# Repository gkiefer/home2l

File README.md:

What are the *Home2Ls*?
=======================

The *Home2L `[houmtu:l]`* suite is a collection of tools and libraries for automation in private homes. Its main features are:

* **_Home2L Resources_**: Novel concept to integrate and manage sensors, actors or services of any kind **efficiently and precisely**.

* **Automation rules written in Python** - but not limited to that.

* **Easy integration of services and new devices** - via MQTT, in C/C++, Python or by a shell script.

* **_Home2L Brownies_**: Simple and efficient **automation bus to interconnect cheap 8-bit microcontrollers**
  for do-it-yourself sensor or actor hardware.

* **_Home2L WallClock_**: **Lightweight, concise, and responsive information display**,
  suitable to be installed on cheap tablets or minicomputers and mounted in all rooms - just like a wall clock.

* **Interactive floor plan** for all kinds of gadgets (windows, shades, lights, phones, computers, services, ...).

* **Video door phone** and **inter-room communication** (SIP-based).

* **Playing music** anywhere at home (MPD-based).

* **Family calendar** (in *WallClock*).

* **Docker image** and improved tutorial for getting started quickly.

What is New?
============

* WallClock: Power meter for votovoltaic systems

* WallClock: User-configurable floorplan icons

* WallClock: Improved and more self-contained Android app

* MQTT bridge: Support for JSON payloads

* New drivers: Fingerprint, Fronius

* Many small improvements and some bug fixes

How Can I Try It? Get More Information?
=======================================

The main place of documentation is the [*Home2L Book*](home2l-book.pdf).
The APIs for developing rules and drivers or to extend the *Home2Ls* are documented with Doxygen:
[C/C++ API](home2l-api_c/index.html), [Python API](home2l-api_python/index.html).

The suite comes with a [Docker Demo Image](https://hub.docker.com/r/gkiefer/home2l) allowing to test the suite easily.
The [*Home2L Book*](home2l-book.pdf) contains a **a step-by-step tutorial demonstrating the key features of the *Home2L* suite**.

**For the brave and the impatient:**

    $ xhost +local:  # allow X11 applications to open windows
    $ docker run -ti --rm \
      --name home2l-showcase --hostname home2l-showcase \
      -e DISPLAY=$DISPLAY -v /tmp/.X11-unix:/tmp/.X11-unix \
      --ipc=host --device /dev/snd \
      gkiefer/home2l

What is Special About the *Home2Ls*?
====================================

## Versatile *Resources* Library

The central component of the *Home2L* suite is the *Resources* library. It connects physical sensors and actors, software services, computers and more. Everything that can act or sense in the widest sense, can be modelled as a *resource* in the *Home2L* suite.

All *resources* are arranged in a common namespace, but driven and accessed in a completely distribited way from any computer. They can be manipulated or read out using the library, which provides full network transparency and supports arbitrary concurrent accesses from any process on any machine anytime.

Resources are manipulated by means of independent *requests* with individual attributes like priorities and time intervals. The user pushes a button to open the window blinds. One second later, a timer-triggered automatic rule tells the blinds to close. What should happen now? The *request* model allows to clearly specify priorities (e.g. user interaction in favor of automation rules) and to handle concurrency properly.

The *Home2L Shell* is a powerful administration tool and allows to access resources and submit requests on the command line or by shell scripts.

Both automation rules and resource drivers can also be part of a larger program. Any software linking against the *Resources* library can access resources or publish own run-time information as resources.

## Efficient and Lightweight Design

All core components are written in C/C++, with a very minimum set of external dependencies beyond *libc* - ideally suited for small embedded devices and microcontrollers. There is no need for a Java runtime environment or a heavy web framework. Starting up a server and a command shell and shutting both down again takes less than a second altogether - on an ARM-based minicomputer running at 144 MHz!

The *Home2L WallClock* is written in native code (C++) and only uses *SDL2* for its UI toolkit. This makes it very portable and lightweight. Low-cost, low-performance minicomputers or Android tablets can be used as end-user devices, there is no need to install and regularly update a full-featured web browser on them.

## Ambient Intelligence, No Need for a Central Server

Central servers are single points of failure. *Home2L* follows a completely distributed concept. Any (mini-)computer can act as part of the network. If resources, such as sensors or actors, are connected to them, they can be exported to any other host in the *Home2L* network. A failure of a host only causes its own resources to be unavailable - everything else keeps on working.

## Automation Rules Written in Python - But Not Limited to That

There is no new language or tool to learn to formulate automation rules. *Home2L* rules written in Python profit from the simplicity and power of the Python language. There can be multiple rules scripts, they can run on any machine, and they may be combined with other software routines or be part of larger applications.

Other ways to interact with *Home2L* resources is via the C/C++ API from any application or by shell scripts using the *Home2L Shell*.

## Integrating Sensors/Actor Hardware and Services: MQTT, Python, Shell Scripts, ...

MQTT-enabled devices can be imported directly using the MQTT gateway driver.

An API for *resource* drivers allows to easily add support for new hardware or services. A driver can be implemented

- in native C/C++ code,
- as a shell script,
- in Python.

For all three cases, documented examples are available in the source tree.

## Easy Integration of Do-It-Yourself Hardware

*Home2L Brownies* are programmed low-cost microcontrollers (*AVR ATtiny 84/85/861*) connected to a Linux host over 4-wire cables (e.g. KNX/EIB cables). The bus protocol is based on *i2c*, robust and allows to build very simple, self-made hardware nodes. Just an *ATtiny* device and two resistors are enough to build a sensor node! Additional circuitry such as crystal clock generators, transceivers or voltage regulators are not necessary.

*Home2L Brownies* can drive, for example, window/door/light sensors (GPIOs), temperature sensors, or window shades/actuators.

The *Home2L* suite includes a software stack for the Linux (host) and for the microcontroller (device) side. The protocol includes various mechanisms for error correction/avoidance, host notification, as well as a variety of maintenance tools for remote configuration, diagnosis, collection of statistics, remote software updates, and device resurrection for the case that a software update failed and the device is difficult to reach physically.

## Privacy

The *Home2Ls* do not need an Internet connection and do not try to communicate with hosts other than they are configured to. By design, the *Home2Ls* communicate with each other over a (trusted) LAN, which can easily be set up and secured using standard Linux/UNIX techniques. The open source licensing ensures transparency for what the software does inside the user's private home.

## Modularity

The core part, the *Resources* library, is kept small and portable with APIs for application programs *and* drivers in C/C++ and Python. All other components are optional and can be used or replaced by alternatives as desired by the user.

How can I Help?
===============

The code has been published with the hope that is useful to the community. To let the project grow further and make available to a broader audience, **volunteers and partners are welcome**.

Great contributions are:

- **Report and help fixing bugs.**

- Make **sample installations**, document them and share your experiences.

- **Packaging**: Create packages for major Linux distributions.

- **Documentation**: Write good documentation, particularly for end users.

For any questions on how to participate, do not hesitate to contact us directly.

Questions?
==========

Feel free to contact: Gundolf Kiefer `<gundolf.kiefer@web.de>`

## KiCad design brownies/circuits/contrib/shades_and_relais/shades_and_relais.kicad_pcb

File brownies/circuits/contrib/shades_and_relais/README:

Circuit:  shades_and_relais/README
Author:   Axel Rau <Axel.Rau+home2l@Chaos1.DE>
Date:     2022-07-29
Updated:  2024-05-27

Description:
  Window Control Board suited for housing CAMDENBOSS CBEAC-03-WH.
  https://www.reichelt.de/elektronikgehaeuse-130x80x45-mm-weiss-cb-eac-03-wh-p317686.html
  It drives one shade with its relais (J1) and has sensors for "window closed"
  (J1 9), "window locked" (J1 8), sun sensor (J1 11) and "shade down and
  "shade up" (J1 6,7), with both wires optional terminated by opto couplers,
  to allow long wirings.
  
  A suitable firmware definition in Family.mk is winl:
  
  # winl: Window brownie; supports temperature sensor and single shade with lock,
  # close and sun sensors (PA3, PA7 and PB2)
  #   - circuit: 'minishades' and 'shades_and_relais'
  ifeq ($(BROWNIE_VARIANT),winl)
  	BROWNIE_CFG ?= WITH_TEMP_ZACWIRE=1 SHADES_PORTS=1 GPIO_IN_PRESENCE=0xc8 GPIO_IN_PULLUP=0xc8 
  	# SHADES_TIMEOUT=0 TWI_SL_NOTIFY=0
  endif

KiCad version: 8

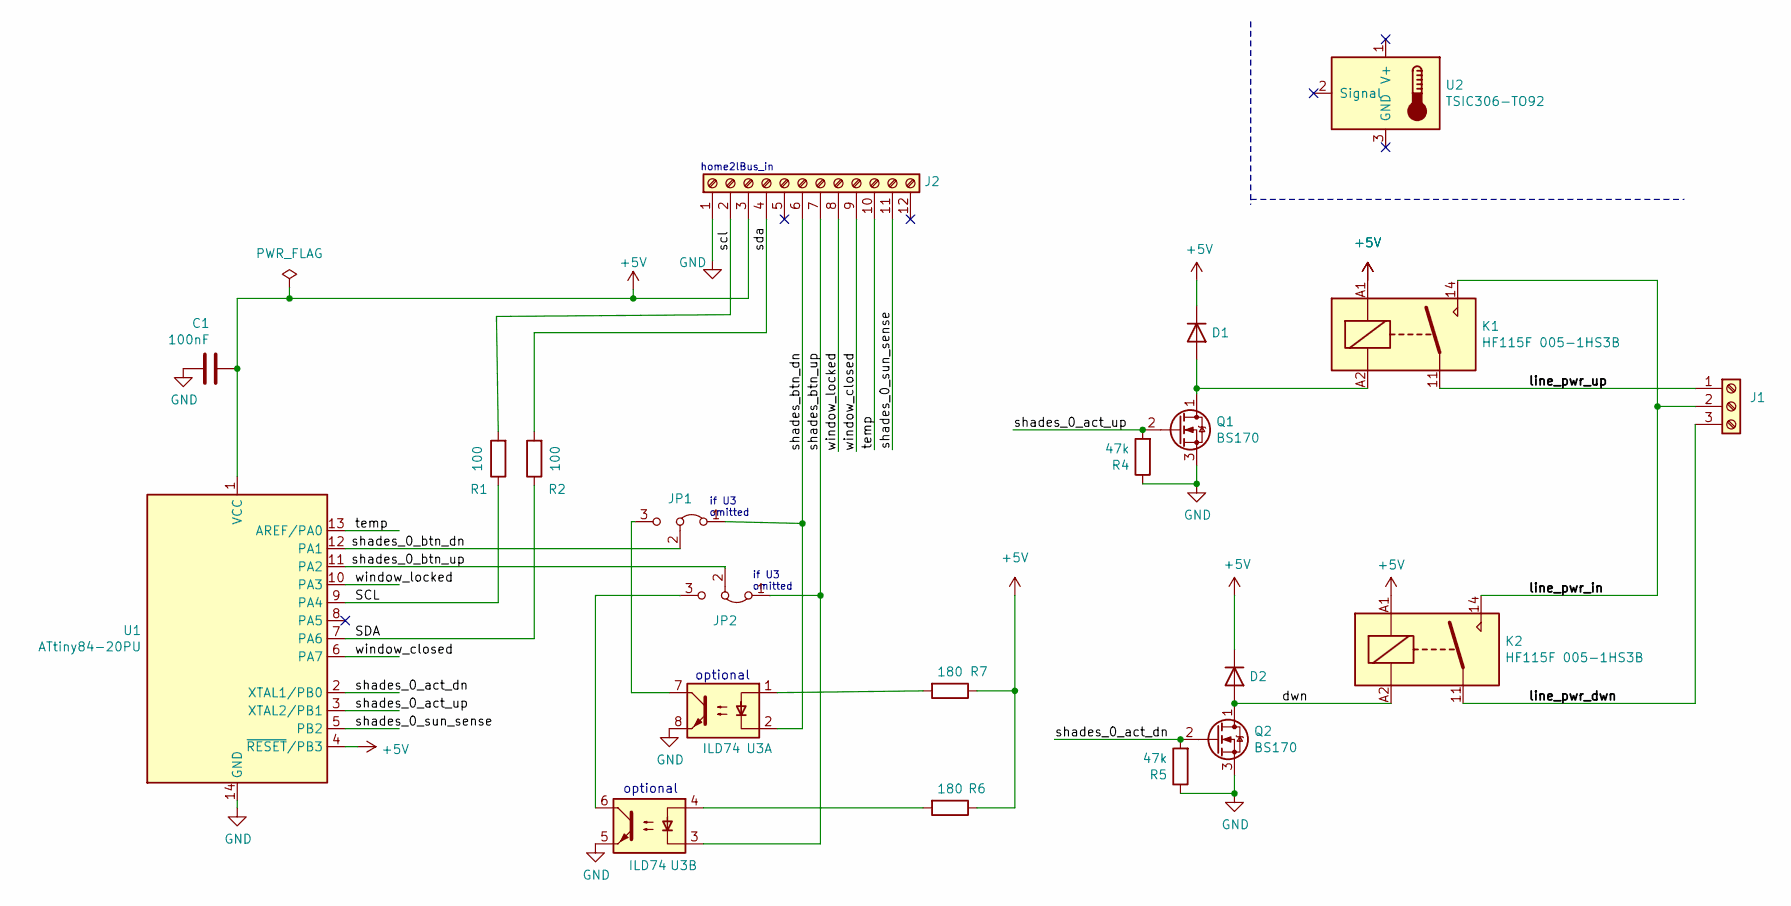
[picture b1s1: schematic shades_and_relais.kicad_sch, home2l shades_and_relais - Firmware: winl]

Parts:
C1: 100nF; C_Disc_D4.3mm_W1.9mm_P5.00mm
D1, D2: 1N400X; D_T-1_P5.08mm_Horizontal
J1: TerminalBlock_bornier-3_P5.08mm
J2: TerminalBlock_Phoenix_MPT-0,5-12-2.54_1x12_P2.54mm_Horizont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
JP1, JP2: PinHeader_1x03_P2.54mm_Vertical
K1, K2: HF115F 005-1HS3B; Relay_SPST_Schrack-RP-II-1-16A-FormA_RM5mm
Q1, Q2: BS170; TO-92_Inline_Wide
R1, R2: 100; R_Axial_DIN0204_L3.6mm_D1.6mm_P7.62mm_Horizontal
R4, R5: 47k; R_Axial_DIN0204_L3.6mm_D1.6mm_P7.62mm_Horizontal
R6, R7: 180; R_Axial_DIN0204_L3.6mm_D1.6mm_P7.62mm_Horizontal
U1: ATtiny84-20PU; DIP-14_W7.62mm_Socket
U2: TSIC306-TO92; TO-92_Inline_Wide
U3: ILD74; DIP-8_W7.62mm

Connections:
+5V: C1.1, D1.1 (K), D2.1 (K), J2.3, K1.A1, K2.A1, R6.1, R7.1, U1.1 (VCC), U1.4 (~RESET/PB3)
/SCL: R1.1, U1.9 (PA4)
/SDA: R2.1, U1.7 (PA6)
/dwn: D2.2 (A), K2.A2, Q2.1 (D)
/line_pwr_dwn: J1.3, K2.11
/line_pwr_in: J1.2, K1.14, K2.14
/line_pwr_up: J1.1, K1.11
/scl: J2.2, R1.2
/sda: J2.4, R2.2
/shades_0_act_dn: Q2.2 (G), R5.2, U1.2 (XTAL1/PB0)
/shades_0_act_up: Q1.2 (G), R4.2, U1.3 (XTAL2/PB1)
/shades_0_btn_dn: JP1.2 (C), U1.12 (PA1)
/shades_0_btn_up: JP2.2 (C), U1.11 (PA2)
/shades_0_sun_sense: J2.11, U1.5 (PB2)
/shades_btn_dn: J2.6, JP1.1 (A), U3.2
/shades_btn_up: J2.7, JP2.1 (A), U3.3
/temp: J2.10, U1.13 (AREF/PA0)
/window_closed: J2.9, U1.6 (PA7)
/window_locked: J2.8, U1.10 (PA3)
GND: C1.2, J2.1, Q1.3 (S), Q2.3 (S), R4.1, R5.1, U1.14 (GND), U3.5, U3.8
unnamed: D1.2 (A), K1.A2, Q1.1 (D)
unnamed: JP1.3 (B), U3.7
unnamed: JP2.3 (B), U3.6
unnamed: R6.2, U3.4
unnamed: R7.2, U3.1

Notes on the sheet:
optional
if U3 omitted
home2lBus_in

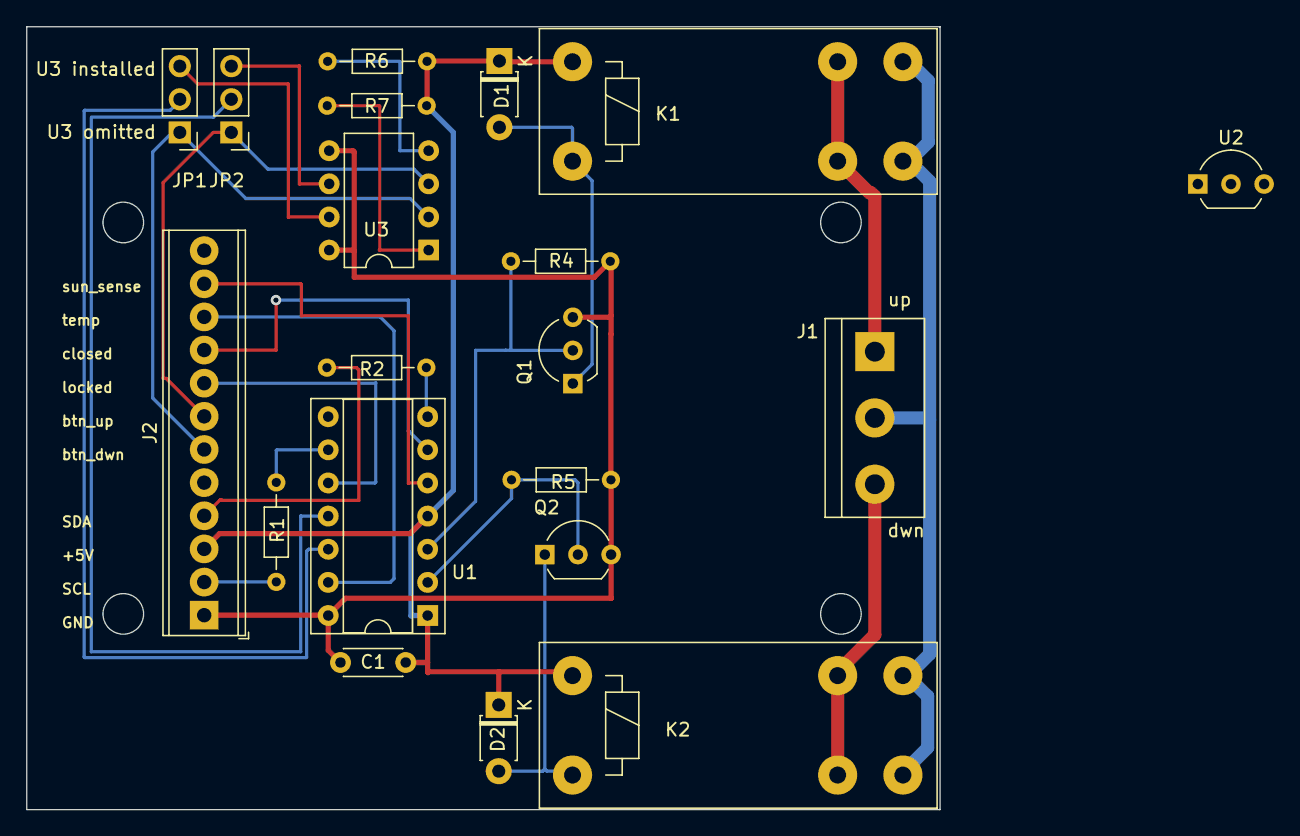
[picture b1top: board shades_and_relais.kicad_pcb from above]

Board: 2 copper layers, 70.0 x 60.0 mm, 20 parts (0 on the bottom side), 25 nets.

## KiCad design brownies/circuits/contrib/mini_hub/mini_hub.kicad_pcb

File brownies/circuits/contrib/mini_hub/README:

Circuit:  mini_hub
Author:   Axel Rau <Axel.Rau+home2l@Chaos1.DE>
Date:     2022-07-29
Updated:  2024-05-26

Description:
  Tiny B-hub Board suited for Spelsberg connection box Q 4-L (33490401).
  
KiCad version: 8

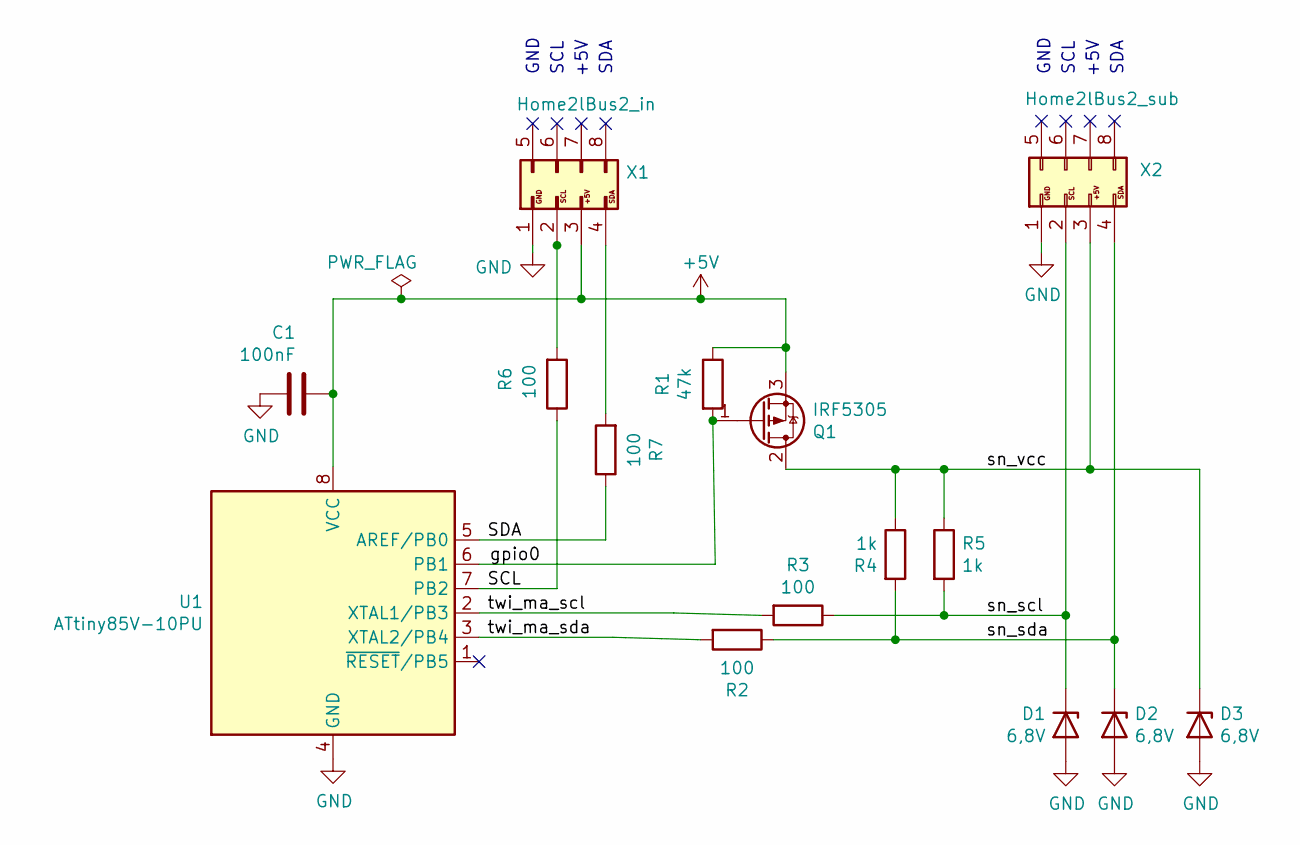
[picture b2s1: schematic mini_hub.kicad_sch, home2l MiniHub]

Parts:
C1: 100nF; C_Disc_D4.3mm_W1.9mm_P5.00mm
D1, D2, D3: 6,8V; D_DO-34_SOD68_P7.62mm_Horizontal
Q1: IRF5305; TO-220-3_Vertical
R1: 47k; R_Axial_DIN0207_L6.3mm_D2.5mm_P7.62mm_Horizontal
R2, R3, R6, R7: 100; R_Axial_DIN0207_L6.3mm_D2.5mm_P7.62mm_Horizontal
R4, R5: 1k; R_Axial_DIN0207_L6.3mm_D2.5mm_P7.62mm_Horizontal
U1: ATtiny85V-10PU; DIP-8_W7.62mm_Socket
X1: Home2lBus2_in; PinHeader_Home2lBus2_in
X2: Home2lBus2_sub; PinSocket_Home2lBus2_sub

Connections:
+5V: C1.1, Q1.3 (S), R1.1, U1.8 (VCC), X1.3
/SCL: R6.1, U1.7 (PB2)
/SDA: R7.1, U1.5 (AREF/PB0)
/gpio0: Q1.1 (G), R1.2, U1.6 (PB1)
/sn_scl: D1.1 (K), R3.1, R5.2, X2.2
/sn_sda: D2.1 (K), R2.1, R4.2, X2.4
/sn_vcc: D3.1 (K), Q1.2 (D), R4.1, R5.1, X2.3
/twi_ma_scl: R3.2, U1.2 (XTAL1/PB3)
/twi_ma_sda: R2.2, U1.3 (XTAL2/PB4)
GND: C1.2, D1.2 (A), D2.2 (A), D3.2 (A), U1.4 (GND), X1.1, X2.1
unnamed: R6.2, X1.2
unnamed: R7.2, X1.4

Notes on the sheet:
SCL
SDA
GND
+5V

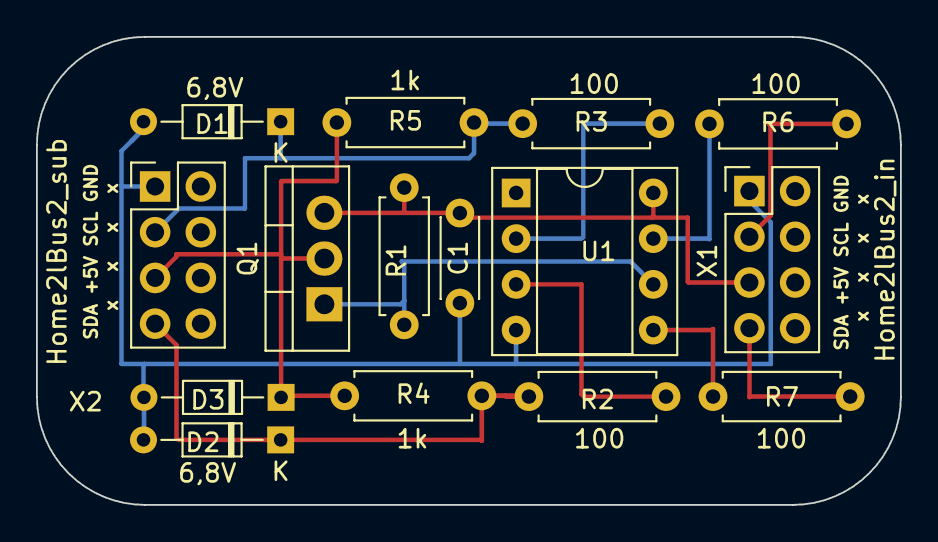
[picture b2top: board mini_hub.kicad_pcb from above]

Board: 2 copper layers, 48.0 x 26.0 mm, 15 parts (0 on the bottom side), 12 nets.

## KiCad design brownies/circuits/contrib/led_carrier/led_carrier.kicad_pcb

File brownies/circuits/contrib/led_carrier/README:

Circuit:  led_carrier
Author:   Axel Rau <Axel.Rau+home2l@Chaos1.DE>
Date:     2022-07-29
Updated:  2024-05-26

Description:
  Design and layout for a small board with multi color LED
  showing green (ready) or green+red=orange (active) for
  1 roomlight. Board mechanically attaches to Gira 0151
  push button. Works together with mini_light 1.2 board, 
  which drives up to 3 groups of led_carrier boards for up
  to 3 room lights. led_carrier boards of one group are wired
  in parallel.

KiCad Version: 8

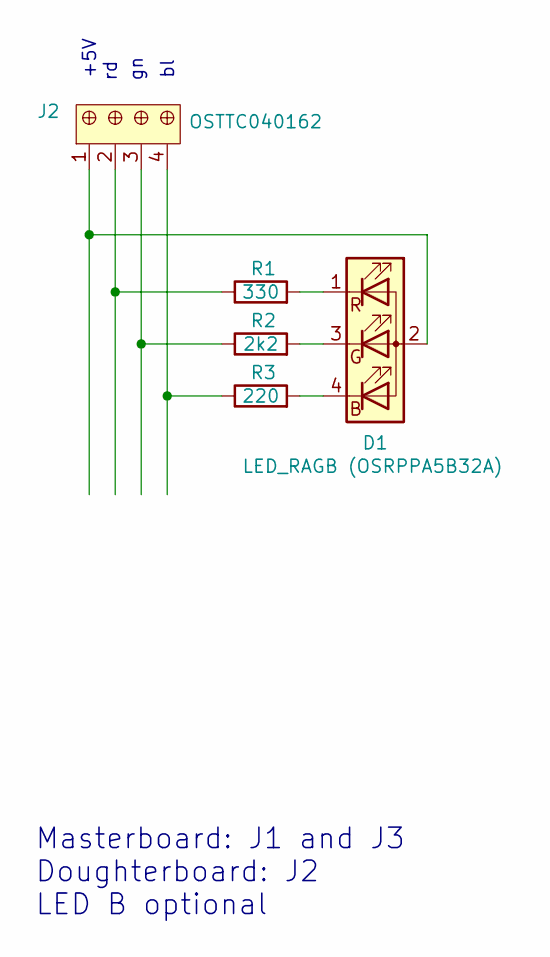
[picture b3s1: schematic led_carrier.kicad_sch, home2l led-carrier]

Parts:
D1: LED_RAGB (OSRPPA5B32A); LED_D5.0mm-4_RGB_Wide_Pins
J2: OSTTC040162; Term_Block_1x4_P5mm; MPN OSTTC040162; Digi-Key_PN ED2602-ND
R1: 330; R_Axial_DIN0204_L3.6mm_D1.6mm_P7.62mm_Horizontal
R2: 2k2; R_Axial_DIN0204_L3.6mm_D1.6mm_P7.62mm_Horizontal
R3: 220; R_Axial_DIN0204_L3.6mm_D1.6mm_P7.62mm_Horizontal

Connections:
unnamed: D1.1 (RK), R1.2
unnamed: D1.2 (A), J2.1
unnamed: D1.3 (GK), R2.2
unnamed: D1.4 (BK), R3.2
unnamed: J2.2, R1.1
unnamed: J2.3, R2.1
unnamed: J2.4, R3.1

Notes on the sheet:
+5V
Masterboard: J1 and J3 Doughterboard: J2 LED B optional

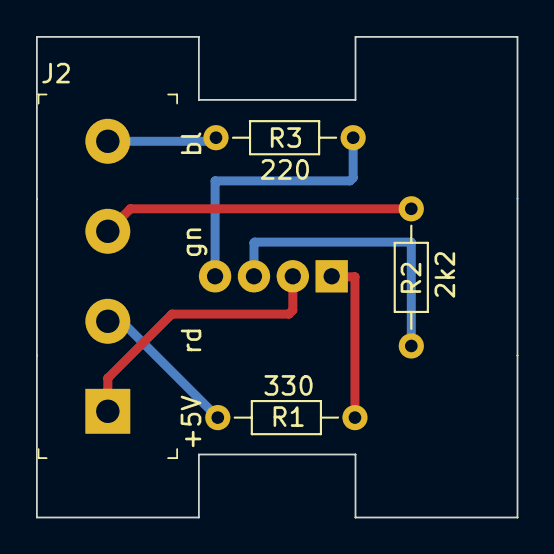
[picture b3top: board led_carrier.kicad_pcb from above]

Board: 2 copper layers, 26.7 x 26.7 mm, 5 parts (1 on the bottom side), 7 nets.

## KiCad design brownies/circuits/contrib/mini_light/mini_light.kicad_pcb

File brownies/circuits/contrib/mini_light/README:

Circuit:  mini_light
Author:   Axel Rau <Axel.Rau+home2l@Chaos1.DE>
Date:     2022-07-29
Updated:  2024-05-26

Description:
  Tiny Room Light Control Board suited for Spelsberg
  connection box Q 4-L (33490401).
  It drives up to 3 bistable relais (J2 10-12) with
  pulse control and control contact (like those from Eltako or ABB).I use
  24V coils.
  mini_light reads signal from control contact via Optp-
  coupler (J2 1-3) to allow long wires.
  Lights are controlled via push buttons with control LED
  like GIRA 0151. Operation is failsafe (works w/o home2l).
  led_carrier board provides the 2 color control LED.
  Control LEDS are connected via J2 5-7(red) and J2 8 (green).
  
  Suitable pin config in Family.mk:
  # minilight: Room Light master for 4 Lights with LEDs and Relais with feedback
  # contact; contacts: PA_0...PA_3, LEDs: PA4...PA7 and 3 coils: PB3...PB5),
  # (PB_2) an t861
  #   - circuit: 'minilight'
    ifeq ($(BROWNIE_VARIANT),minilight)
	   BROWNIE_CFG ?= GPIO_OUT_PRESENCE=0x7f0 GPIO_OUT_PRESET=0x0f0 GPIO_IN_PRESENCE=0x00f GPIO_IN_PULLUP=0x00f
    endif

KiCad version: 8

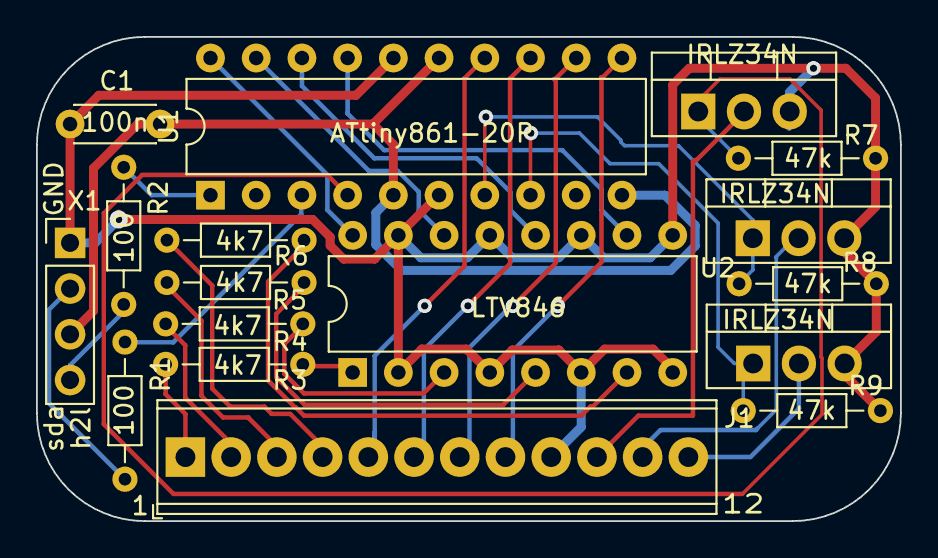
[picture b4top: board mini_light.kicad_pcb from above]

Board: 2 copper layers, 48.0 x 26.9 mm, 17 parts (0 on the bottom side), 28 nets.

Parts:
C1: 100nF; C_Disc_D4.3mm_W1.9mm_P5.00mm
IRLZ34N, IRLZ34N#2, IRLZ34N#3: IRLZ34N; TO-220-3_Vertical
J1: TerminalBlock_Phoenix_MPT-0,5-12-2.54_1x12_P2.54mm_Horizont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
R1, R2: 100; R_Axial_DIN0204_L3.6mm_D1.6mm_P7.62mm_Horizontal
R3, R4, R5, R6: 4k7; R_Axial_DIN0204_L3.6mm_D1.6mm_P7.62mm_Horizontal
R7, R8, R9: 47k; R_Axial_DIN0204_L3.6mm_D1.6mm_P7.62mm_Horizontal
U1: ATtiny861-20P; DIP-20_W7.62mm
U2: LTV-847; DIP-16_W7.62mm
X1: Home2lBus2_in; PinHeader_1x04_P2.54mm_Vertical

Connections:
+5V: C1.1, U1.5 (VCC), U1.10 (~RESET/PB7), U1.15 (AVCC), X1.3
/scl: R1.2, X1.2
/sda: R2.2, X1.4
GND: C1.2, IRLZ34N.3 (S), IRLZ34N#2.3 (S), IRLZ34N#3.3 (S), J1.9, R7.1, R8.1, R9.1, U1.6 (GND), U1.16 (AGND), U2.2, U2.4, U2.6, U2.8, U2.9, U2.11, U2.13, U2.15, X1.1
unnamed: J1.1, R3.1
unnamed: J1.2, R4.1
unnamed: J1.3, R5.1
unnamed: J1.4, R6.1
unnamed: J1.5, U1.14 (PA4)
unnamed: J1.6, U1.13 (PA5)
unnamed: J1.7, U1.12 (PA6)
unnamed: J1.8, U1.11 (PA7)
unnamed: IRLZ34N#3.2 (D), J1.10
unnamed: IRLZ34N.2 (D), J1.11
unnamed: IRLZ34N#2.2 (D), J1.12
unnamed: R1.1, U1.3 (PB2)
unnamed: R2.1, U1.1 (PB0)
unnamed: R3.2, U2.1
unnamed: R4.2, U2.3
unnamed: R5.2, U2.5
unnamed: R6.2, U2.7
unnamed: IRLZ34N#3.1 (G), R7.2, U1.4 (PB3)
unnamed: IRLZ34N.1 (G), R8.2, U1.7 (XTAL1/PB4)
unnamed: IRLZ34N#2.1 (G), R9.2, U1.8 (XTAL2/PB5)
unnamed: U1.17 (AREF/PA3), U2.10
unnamed: U1.18 (PA2), U2.12
unnamed: U1.19 (PA1), U2.14
unnamed: U1.20 (PA0), U2.16

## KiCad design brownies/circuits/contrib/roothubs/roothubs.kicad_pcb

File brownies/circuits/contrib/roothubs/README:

Circuit:  roothubs
Author:   Axel Rau <Axel.Rau+home2l@Chaos1.DE>
Date:     2022-07-29
Updated:  2024-05-26

Description:
  Design and layout for a card with 11 root hubs.
  Each of the 11 hubs may be separated and used standalone.
  Project structured as KiCad 8 flat hierarchy.

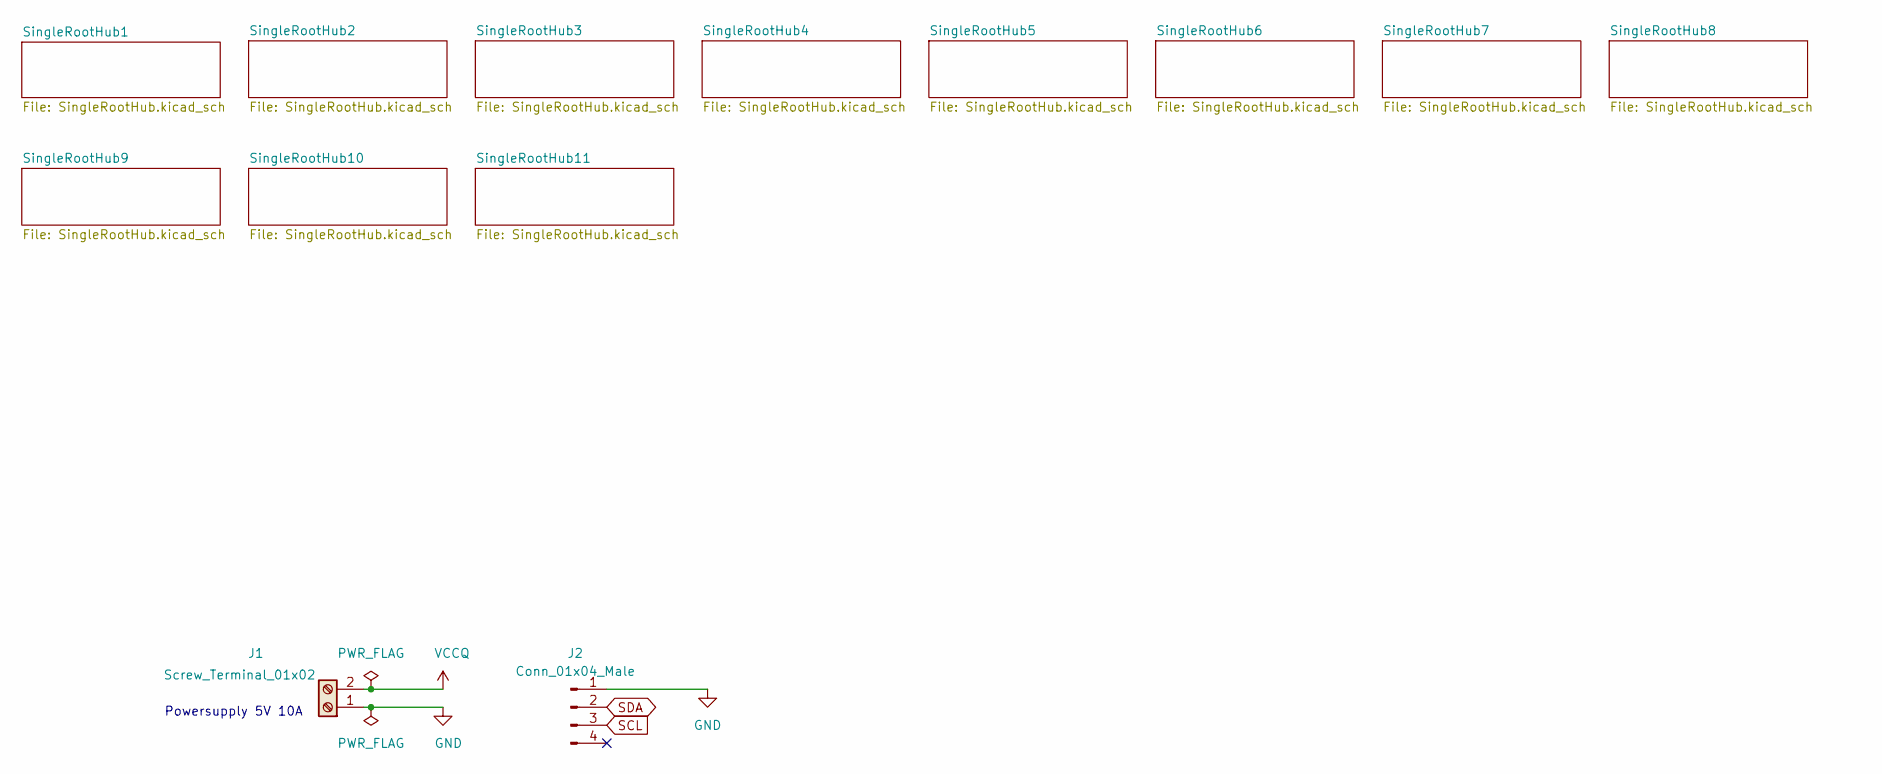
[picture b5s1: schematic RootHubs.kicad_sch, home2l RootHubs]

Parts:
J1: Screw_Terminal_01x02; TerminalBlock_bornier-2_P5.08mm
J2: Conn_01x04_Male; PinHeader_1x04_P2.54mm_Vertical

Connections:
GND: J1.1, J2.1; also elsewhere on the board
SCL: J2.3; also elsewhere on the board
SDA: J2.2; also elsewhere on the board
VCCQ: J1.2; also elsewhere on the board

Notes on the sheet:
Powersupply 5V 10A

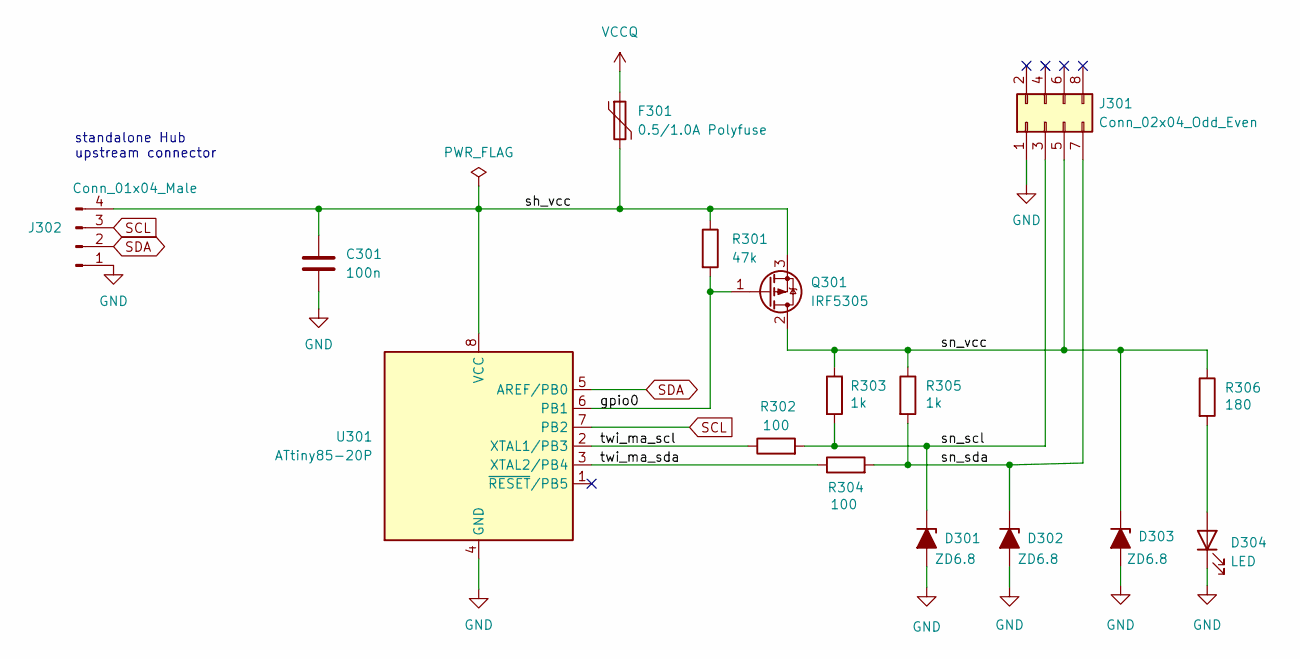
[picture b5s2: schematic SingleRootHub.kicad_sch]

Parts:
C301: 100n; C_Disc_D4.3mm_W1.9mm_P5.00mm
D301, D302, D303: ZD6.8; D_DO-41_SOD81_P7.62mm_Horizontal
D304: LED; LED_D3.0mm
F301: 0.5/1.0A Polyfuse; Polyfuse_Schurter_PFRA
J301: Conn_02x04_Odd_Even; PinSocket_2x04_P2.54mm_Vertical
J302: Conn_01x04_Male; PinHeader_1x04_P2.54mm_Vertical
Q301: IRF5305; TO-220-3_Vertical
R301: 47k; R_Axial_DIN0207_L6.3mm_D2.5mm_P7.62mm_Horizontal
R302, R304: 100; R_Axial_DIN0207_L6.3mm_D2.5mm_P7.62mm_Horizontal
R303, R305: 1k; R_Axial_DIN0207_L6.3mm_D2.5mm_P7.62mm_Horizontal
R306: 180; R_Axial_DIN0207_L6.3mm_D2.5mm_P7.62mm_Horizontal
U301: ATtiny85-20P; DIP-8_W7.62mm

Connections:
/SingleRootHub1/gpio0: Q301.1 (G), R301.2, U301.6 (PB1)
/SingleRootHub1/sh_vcc: C301.1, F301.2, J302.4, Q301.3 (S), R301.1, U301.8 (VCC)
/SingleRootHub1/sn_scl: D301.1 (K), J301.3, R302.2, R303.2
/SingleRootHub1/sn_sda: D302.1 (K), J301.7, R304.2, R305.2
/SingleRootHub1/sn_vcc: D303.1 (K), J301.5, Q301.2 (D), R303.1, R305.1, R306.1
/SingleRootHub1/twi_ma_scl: R302.1, U301.2 (XTAL1/PB3)
/SingleRootHub1/twi_ma_sda: R304.1, U301.3 (XTAL2/PB4)
GND: C301.2, D301.2 (A), D302.2 (A), D303.2 (A), D304.1 (K), J301.1, J302.1, U301.4 (GND); also elsewhere on the board
unnamed: D304.2 (A), R306.2
SCL: J302.3, U301.7 (PB2); also elsewhere on the board
SDA: J302.2, U301.5 (AREF/PB0); also elsewhere on the board
VCCQ: F301.1; also elsewhere on the board

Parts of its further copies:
C201, C401, C501, C601, C701, C801, C901, C1001, C1101, C1201: 100n; C_Disc_D4.3mm_W1.9mm_P5.00mm
D201, D202, D203, D401, D402, D403, D501, D502, D503, D601, D602, D603, D701, D702, D703, D801, D802, D803, D901, D902, D903, D1001, D1002, D1003, D1101, D1102, D1103, D1201, D1202, D1203: ZD6.8; D_DO-41_SOD81_P7.62mm_Horizontal
D204, D404, D504, D604, D704, D804, D904, D1004, D1104, D1204: LED; LED_D3.0mm
F201, F401, F501, F601, F701, F801, F901, F1001, F1101, F1201: 0.5/1.0A Polyfuse; Polyfuse_Schurter_PFRA
J201, J401, J501, J601, J701, J801, J901, J1001, J1101, J1201: Conn_02x04_Odd_Even; PinSocket_2x04_P2.54mm_Vertical
J202, J402, J502, J602, J702, J802, J902, J1002, J1102, J1202: Conn_01x04_Male; PinHeader_1x04_P2.54mm_Vertical
Q201, Q401, Q501, Q601, Q701, Q801, Q901, Q1001, Q1101, Q1201: IRF5305; TO-220-3_Vertical
R201, R401, R501, R601, R701, R801, R901, R1001, R1101, R1201: 47k; R_Axial_DIN0207_L6.3mm_D2.5mm_P7.62mm_Horizontal
R202, R204, R402, R404, R502, R504, R602, R604, R702, R704, R802, R804, R902, R904, R1002, R1004, R1102, R1104, R1202, R1204: 100; R_Axial_DIN0207_L6.3mm_D2.5mm_P7.62mm_Horizontal
R203, R205, R403, R405, R503, R505, R603, R605, R703, R705, R803, R805, R903, R905, R1003, R1005, R1103, R1105, R1203, R1205: 1k; R_Axial_DIN0207_L6.3mm_D2.5mm_P7.62mm_Horizontal
R206, R406, R506, R606, R706, R806, R906, R1006, R1106, R1206: 180; R_Axial_DIN0207_L6.3mm_D2.5mm_P7.62mm_Horizontal
U201, U401, U501, U601, U701, U801, U901, U1001, U1101, U1201: ATtiny85-20P; DIP-8_W7.62mm

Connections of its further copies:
/SingleRootHub2/gpio0: Q201.1 (G), R201.2, U201.6 (PB1)
/SingleRootHub2/sh_vcc: C201.1, F201.2, J202.4, Q201.3 (S), R201.1, U201.8 (VCC)
/SingleRootHub2/sn_scl: D201.1 (K), J201.3, R202.2, R203.2
/SingleRootHub2/sn_sda: D202.1 (K), J201.7, R204.2, R205.2
/SingleRootHub2/sn_vcc: D203.1 (K), J201.5, Q201.2 (D), R203.1, R205.1, R206.1
/SingleRootHub2/twi_ma_scl: R202.1, U201.2 (XTAL1/PB3)
/SingleRootHub2/twi_ma_sda: R204.1, U201.3 (XTAL2/PB4)
/SingleRootHub3/gpio0: Q401.1 (G), R401.2, U401.6 (PB1)
/SingleRootHub3/sh_vcc: C401.1, F401.2, J402.4, Q401.3 (S), R401.1, U401.8 (VCC)
/SingleRootHub3/sn_scl: D401.1 (K), J401.3, R402.2, R403.2
/SingleRootHub3/sn_sda: D402.1 (K), J401.7, R404.2, R405.2
/SingleRootHub3/sn_vcc: D403.1 (K), J401.5, Q401.2 (D), R403.1, R405.1, R406.1
/SingleRootHub3/twi_ma_scl: R402.1, U401.2 (XTAL1/PB3)
/SingleRootHub3/twi_ma_sda: R404.1, U401.3 (XTAL2/PB4)
/SingleRootHub4/gpio0: Q501.1 (G), R501.2, U501.6 (PB1)
/SingleRootHub4/sh_vcc: C501.1, F501.2, J502.4, Q501.3 (S), R501.1, U501.8 (VCC)
/SingleRootHub4/sn_scl: D501.1 (K), J501.3, R502.2, R503.2
/SingleRootHub4/sn_sda: D502.1 (K), J501.7, R504.2, R505.2
/SingleRootHub4/sn_vcc: D503.1 (K), J501.5, Q501.2 (D), R503.1, R505.1, R506.1
/SingleRootHub4/twi_ma_scl: R502.1, U501.2 (XTAL1/PB3)
/SingleRootHub4/twi_ma_sda: R504.1, U501.3 (XTAL2/PB4)
/SingleRootHub5/gpio0: Q601.1 (G), R601.2, U601.6 (PB1)
/SingleRootHub5/sh_vcc: C601.1, F601.2, J602.4, Q601.3 (S), R601.1, U601.8 (VCC)
/SingleRootHub5/sn_scl: D601.1 (K), J601.3, R602.2, R603.2
/SingleRootHub5/sn_sda: D602.1 (K), J601.7, R604.2, R605.2
/SingleRootHub5/sn_vcc: D603.1 (K), J601.5, Q601.2 (D), R603.1, R605.1, R606.1
/SingleRootHub5/twi_ma_scl: R602.1, U601.2 (XTAL1/PB3)
/SingleRootHub5/twi_ma_sda: R604.1, U601.3 (XTAL2/PB4)
/SingleRootHub6/gpio0: Q701.1 (G), R701.2, U701.6 (PB1)
/SingleRootHub6/sh_vcc: C701.1, F701.2, J702.4, Q701.3 (S), R701.1, U701.8 (VCC)
/SingleRootHub6/sn_scl: D701.1 (K), J701.3, R702.2, R703.2
/SingleRootHub6/sn_sda: D702.1 (K), J701.7, R704.2, R705.2
/SingleRootHub6/sn_vcc: D703.1 (K), J701.5, Q701.2 (D), R703.1, R705.1, R706.1
/SingleRootHub6/twi_ma_scl: R702.1, U701.2 (XTAL1/PB3)
/SingleRootHub6/twi_ma_sda: R704.1, U701.3 (XTAL2/PB4)
/SingleRootHub7/gpio0: Q801.1 (G), R801.2, U801.6 (PB1)
/SingleRootHub7/sh_vcc: C801.1, F801.2, J802.4, Q801.3 (S), R801.1, U801.8 (VCC)
/SingleRootHub7/sn_scl: D801.1 (K), J801.3, R802.2, R803.2
/SingleRootHub7/sn_sda: D802.1 (K), J801.7, R804.2, R805.2
/SingleRootHub7/sn_vcc: D803.1 (K), J801.5, Q801.2 (D), R803.1, R805.1, R806.1
/SingleRootHub7/twi_ma_scl: R802.1, U801.2 (XTAL1/PB3)
/SingleRootHub7/twi_ma_sda: R804.1, U801.3 (XTAL2/PB4)
/SingleRootHub8/gpio0: Q901.1 (G), R901.2, U901.6 (PB1)
/SingleRootHub8/sh_vcc: C901.1, F901.2, J902.4, Q901.3 (S), R901.1, U901.8 (VCC)
/SingleRootHub8/sn_scl: D901.1 (K), J901.3, R902.2, R903.2
/SingleRootHub8/sn_sda: D902.1 (K), J901.7, R904.2, R905.2
/SingleRootHub8/sn_vcc: D903.1 (K), J901.5, Q901.2 (D), R903.1, R905.1, R906.1
/SingleRootHub8/twi_ma_scl: R902.1, U901.2 (XTAL1/PB3)
/SingleRootHub8/twi_ma_sda: R904.1, U901.3 (XTAL2/PB4)
/SingleRootHub9/gpio0: Q1001.1 (G), R1001.2, U1001.6 (PB1)
/SingleRootHub9/sh_vcc: C1001.1, F1001.2, J1002.4, Q1001.3 (S), R1001.1, U1001.8 (VCC)
/SingleRootHub9/sn_scl: D1001.1 (K), J1001.3, R1002.2, R1003.2
/SingleRootHub9/sn_sda: D1002.1 (K), J1001.7, R1004.2, R1005.2
/SingleRootHub9/sn_vcc: D1003.1 (K), J1001.5, Q1001.2 (D), R1003.1, R1005.1, R1006.1
/SingleRootHub9/twi_ma_scl: R1002.1, U1001.2 (XTAL1/PB3)
/SingleRootHub9/twi_ma_sda: R1004.1, U1001.3 (XTAL2/PB4)
/SingleRootHub10/gpio0: Q1101.1 (G), R1101.2, U1101.6 (PB1)
/SingleRootHub10/sh_vcc: C1101.1, F1101.2, J1102.4, Q1101.3 (S), R1101.1, U1101.8 (VCC)
/SingleRootHub10/sn_scl: D1101.1 (K), J1101.3, R1102.2, R1103.2
/SingleRootHub10/sn_sda: D1102.1 (K), J1101.7, R1104.2, R1105.2
/SingleRootHub10/sn_vcc: D1103.1 (K), J1101.5, Q1101.2 (D), R1103.1, R1105.1, R1106.1
/SingleRootHub10/twi_ma_scl: R1102.1, U1101.2 (XTAL1/PB3)
/SingleRootHub10/twi_ma_sda: R1104.1, U1101.3 (XTAL2/PB4)
/SingleRootHub11/gpio0: Q1201.1 (G), R1201.2, U1201.6 (PB1)
/SingleRootHub11/sh_vcc: C1201.1, F1201.2, J1202.4, Q1201.3 (S), R1201.1, U1201.8 (VCC)
/SingleRootHub11/sn_scl: D1201.1 (K), J1201.3, R1202.2, R1203.2
/SingleRootHub11/sn_sda: D1202.1 (K), J1201.7, R1204.2, R1205.2
/SingleRootHub11/sn_vcc: D1203.1 (K), J1201.5, Q1201.2 (D), R1203.1, R1205.1, R1206.1
/SingleRootHub11/twi_ma_scl: R1202.1, U1201.2 (XTAL1/PB3)
/SingleRootHub11/twi_ma_sda: R1204.1, U1201.3 (XTAL2/PB4)
GND: C201.2, C401.2, C501.2, C601.2, C701.2, C801.2, C901.2, C1001.2, C1101.2, C1201.2, D201.2 (A), D202.2 (A), D203.2 (A), D204.1 (K), D401.2 (A), D402.2 (A), D403.2 (A), D404.1 (K), D501.2 (A), D502.2 (A), D503.2 (A), D504.1 (K), D601.2 (A), D602.2 (A), D603.2 (A), D604.1 (K), D701.2 (A), D702.2 (A), D703.2 (A), D704.1 (K), D801.2 (A), D802.2 (A), D803.2 (A), D804.1 (K), D901.2 (A), D902.2 (A), D903.2 (A), D904.1 (K), D1001.2 (A), D1002.2 (A), D1003.2 (A), D1004.1 (K), D1101.2 (A), D1102.2 (A), D1103.2 (A), D1104.1 (K), D1201.2 (A), D1202.2 (A), D1203.2 (A), D1204.1 (K), J201.1, J202.1, J401.1, J402.1, J501.1, J502.1, J601.1, J602.1, J701.1, J702.1, J801.1, J802.1, J901.1, J902.1, J1001.1, J1002.1, J1101.1, J1102.1, J1201.1, J1202.1, U201.4 (GND), U401.4 (GND), U501.4 (GND), U601.4 (GND), U701.4 (GND), U801.4 (GND), U901.4 (GND), U1001.4 (GND), U1101.4 (GND), U1201.4 (GND); also elsewhere on the board
unnamed: D204.2 (A), R206.2
unnamed: D404.2 (A), R406.2
unnamed: D504.2 (A), R506.2
unnamed: D604.2 (A), R606.2
unnamed: D704.2 (A), R706.2
unnamed: D804.2 (A), R806.2
unnamed: D904.2 (A), R906.2
unnamed: D1004.2 (A), R1006.2
unnamed: D1104.2 (A), R1106.2
unnamed: D1204.2 (A), R1206.2
SCL: J202.3, J402.3, J502.3, J602.3, J702.3, J802.3, J902.3, J1002.3, J1102.3, J1202.3, U201.7 (PB2), U401.7 (PB2), U501.7 (PB2), U601.7 (PB2), U701.7 (PB2), U801.7 (PB2), U901.7 (PB2), U1001.7 (PB2), U1101.7 (PB2), U1201.7 (PB2); also elsewhere on the board
SDA: J202.2, J402.2, J502.2, J602.2, J702.2, J802.2, J902.2, J1002.2, J1102.2, J1202.2, U201.5 (AREF/PB0), U401.5 (AREF/PB0), U501.5 (AREF/PB0), U601.5 (AREF/PB0), U701.5 (AREF/PB0), U801.5 (AREF/PB0), U901.5 (AREF/PB0), U1001.5 (AREF/PB0), U1101.5 (AREF/PB0), U1201.5 (AREF/PB0); also elsewhere on the board
VCCQ: F201.1, F401.1, F501.1, F601.1, F701.1, F801.1, F901.1, F1001.1, F1101.1, F1201.1; also elsewhere on the board

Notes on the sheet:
standalone Hub upstream connector

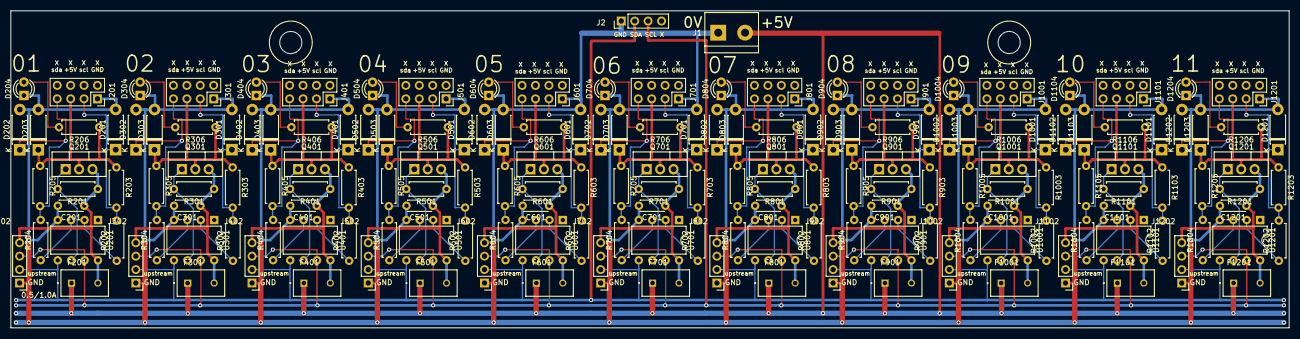
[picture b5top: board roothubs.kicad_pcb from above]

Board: 2 copper layers, 242.0 x 60.0 mm, 178 parts (0 on the bottom side), 92 nets.
